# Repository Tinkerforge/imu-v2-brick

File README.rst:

IMU Brick 2.0
=============

This repository contains the firmware source code and the hardware design
files. The documentation generator configs can be found at
https://github.com/Tinkerforge/generators

Repository Content
------------------

software/:
 * examples/: Examples for all supported languages
 * build/: Compiled files
 * src/: Source code of firmware
 * Makefile: Makefile to build project

hardware/:
 * Contains KiCad project files and additionally schematics as PDF

datasheets/:
 * Contains datasheets for sensors and complex ICs that are used

Hardware
--------

The hardware is designed with the open source EDA Suite KiCad
(http://www.kicad.org). Before you are able to open the files,
you have to install the Tinkerforge kicad-libraries
(https://github.com/Tinkerforge/kicad-libraries). You can either clone
them directly in hardware/ or clone them in a separate folder and
symlink them into hardware/
(ln -s kicad_path/kicad-libraries project_path/hardware). After that you
can open the .pro file in hardware/ with KiCad and from there view and
modify the schematics and the PCB layout.

Software
--------

If you want to do your own Brick/Bricklet firmware development we highly
recommend that you use our build environment setup script and read the
tutorial (https://www.tinkerforge.com/en/doc/Tutorials/Tutorial_Build_Environment/Tutorial.html).

To compile the C code we recommend you to install the newest GNU Arm Embedded
Toolchain (https://launchpad.net/gcc-arm-embedded/+download).
You also need to install bricklib (https://github.com/Tinkerforge/bricklib).

You can either clone it directly in software/src/ or clone it in a
separate folder and symlink it into software/src/
(ln -s bricklib_path/bricklib project_path/software/src/). Finally make sure to
have CMake installed (http://www.cmake.org/cmake/resources/software.html).

After that you can build the firmware by invoking make in software/.
The firmware (.bin) can then be found in software/build/ and uploaded
with brickv (click button "Flashing" on start screen).

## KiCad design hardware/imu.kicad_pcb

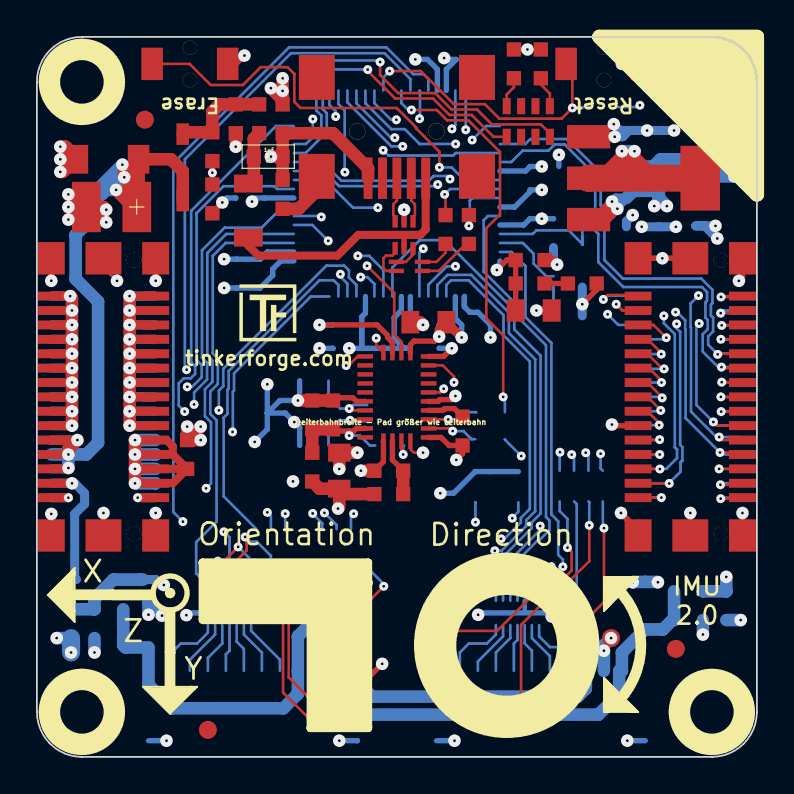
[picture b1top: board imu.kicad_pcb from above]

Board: 4 copper layers, 40.0 x 40.0 mm, 107 parts (0 on the bottom side), 124 nets.

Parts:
C1, C2: DNP; C0603
C3: 1µF; 0603
C4, C401, C402, C403, C404: 1µF; C0603
C5, C6: 22pF; C0603
C7, C8, C14, C17, C18, C19, C20, C22, C23, C24, C26, C27, C29, C30: 100nF; C0603
C9: 6.8nF; C0603
C10: 120nF; C0603
C11: 4.7µF; C0805
C12: 100µF; 3528-21
C13, C16: 10µF; C0805
C15, C28: 4.7µF; C0603
C21: 2.2µF; C0603
C25: 10µF/10V; C0805
D1, D3, D5, D7: blue; D0603
D2, D4, D6, D8: red; D0603
D9, D10, D11, D12: green; D0603
D13, D14: B0520LW-7-F; SOD-123
D15: Z5V; MiniMelf
D16: Z3.3V; MiniMelf
D401: ESD5V0D3B-TP; SOD-323
D402: ESD3V3D3B-TP; SOD-323
F1: PTC; C1206
FB1, FB2, FB4: FB; C0603
FB3: 0; C0603
FB401, FB402: FILTER; C0603
FILTER401, FILTER402: IP4254; DFN16-33x135
Fiducial_Mark: VAL**; Fiducial_Mark
Fiducial_Mark#2, Fiducial_Mark#3, Fiducial_Mark#4, Fiducial_Mark#5, Fiducial_Mark#6: VAL**; Fiducial_Mark
J1: USB-MINI-B-SMD
J2, J3, J4, J5: DRILL; DRILL_NP
J6, J8: STACK-UP-LOW; BTB08-ACS-TOP
J7, J9: STACK-DOWN; BTB08-ACS-BTM
L1: 744230900; WE-CNSW-0603
L2, L3: INDUCTOR; C0603
L4: LBR2012T100K; C0805
P1, P2: CON-SENSOR
R1, R2: 27; R0603
R3: 0; R0603
R4: 47k; R0603
R5: 68k; R0603
R6: 10k; R0603
R7, R8: DNP; R0603
R9: 1k; R0603
R10: 1R0; R0603
RP1, RP2, RP3, RP4, RP5: 1k; 0603X4
SW1: Reset; TACT-SWITCH
SW2: Erase; TACT-SWITCH
U1: AT91SAM3SXB; LQFP64
U2: 82400152; SOT563-SPEC
U3: BNO055; LGA28_5832
U4: LD1117; SOT-223
VAL: CE_5mm
VAL#2: WEEE_7mm
X1: 16Mhz; CRYSTAL_3225
X2: 32.768kHz; AB26TRQ

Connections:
3V3: C11.1, C13.1, C14.1, C15.1, C17.1, C19.1, C20.1, C25.1, C27.1, C30.1, C402.1, D1.1, D2.1, D3.1, D4.1, D5.1, D6.1, D7.1, D8.1, D9.1, D10.1, D11.1, D12.1, D13.1, D16.2, FB402.1, FILTER401.14, J6.20, L2.2, L3.2, RP5.1, RP5.2, RP5.3, RP5.4, SW2.2, U1.1, U1.7, U1.18, U1.45, U1.58, U4.2
BNO-ADR-SELECT: U1.34, U3.17
BNO-BOOT: R6.2, U1.38, U3.4
BNO-INT: U1.26, U3.14
BNO-PIN7: R7.1, U1.52
BNO-PIN8: R8.1, U1.41
BNO-nRESET: U1.35, U3.11
BRICKLET-I2C-SCL: FILTER401.16, FILTER402.16, RP5.5, U1.36, U3.19
BRICKLET-I2C-SDA: FILTER401.15, FILTER402.15, RP5.8, U1.43, U3.20
BRICKLET-IO0_0/AD0: FILTER401.13, U1.4
BRICKLET-IO0_1/DA0: FILTER401.12, U1.63
BRICKLET-IO0_2/PWM0: FILTER401.11, U1.44
BRICKLET-IO0_3: FILTER401.10, U1.19
BRICKLET-IO1_0/AD1: FILTER402.13, U1.3
BRICKLET-IO1_1/DA1: FILTER402.12, U1.59
BRICKLET-IO1_2/PWM1: FILTER402.11, U1.47
BRICKLET-IO1_3: FILTER402.10, U1.9
GND: C1.2, C2.2, C4.2, C5.2, C6.2, C7.2, C8.2, C9.2, C10.2, C11.2, C12.2, C13.2, C14.2, C15.2, C16.2, C17.2, C18.2, C19.2, C20.2, C21.2, C22.2, C23.2, C24.2, C25.2, C26.2, C27.2, C28.2, C29.2, C30.2, C401.2, C402.2, C403.2, C404.2, D15.1, D16.1, D401.1, D402.1, FB3.2, FILTER401.EXP, FILTER402.14, FILTER402.EXP, J6.EP, J7.EP, J8.EP, J9.EP, P1.2, P1.EP, P2.2, P2.EP, R3.1, R5.1, SW1.2, U1.2, U1.17, U1.46, U1.60, U3.2, U3.5, U3.6, U3.10, U3.15, U3.16, U3.18, U3.25, U4.1, X1.3, X2.3
GNDA: C3.2, FB2.1, J1.5, R3.2, U2.2
LED-DEG-1: RP4.1, U1.20
LED-DEG-2: RP4.3, U1.37
LED-DEG-3: RP4.4, U1.48
LED-DEG-4: RP4.2, U1.32
LED-XYZ-XA: RP2.1, U1.15
LED-XYZ-XB: RP2.2, U1.13
LED-XYZ-YA: RP2.3, U1.23
LED-XYZ-YB: RP3.1, U1.16
LED-XYZ-ZA: RP3.2, U1.25
LED-XYZ-ZB: RP3.3, U1.42
unnamed: C3.1, F1.2, FB1.1
unnamed: C5.1, U3.27, X2.2
unnamed: C6.1, U3.26, X2.1
unnamed: C7.1, U3.9
unnamed: C8.1, L3.1, U3.3
unnamed: C9.1, C10.1, L2.1, R6.1, U3.28
unnamed: C21.1, C22.1, C23.1, C24.1, C26.1, L4.1, U1.8, U1.12, U1.24, U1.54
unnamed: C28.1, R10.1
unnamed: C29.1, L4.2, R10.2, U1.64
unnamed: C403.1, D401.2, FB401.2, P1.1, P2.1
unnamed: C404.1, D402.2, FB402.2, P1.3, P2.3
unnamed: D1.2, RP1.1
unnamed: D2.2, RP1.4
unnamed: D3.2, RP2.8
unnamed: D4.2, RP2.7
unnamed: D5.2, RP2.6
unnamed: D6.2, RP3.8
unnamed: D7.2, RP3.7
unnamed: D8.2, RP3.6
unnamed: D9.2, RP4.8
unnamed: D10.2, RP4.7
unnamed: D11.2, RP4.6
unnamed: D12.2, RP4.5
unnamed: D13.2, J8.28, J9.28
unnamed: F1.1, J1.1, U2.5
unnamed: FB2.2, J1.6
unnamed: FB3.1, J8.21, J8.23, J8.25, J8.27, J9.21, J9.23, J9.25, J9.27
unnamed: FB4.2, J8.22, J8.24, J8.26, J9.22, J9.24, J9.26
unnamed: FILTER401.1, P1.4
unnamed: FILTER401.2, P1.5
unnamed: FILTER401.3, P1.6
unnamed: FILTER401.4, P1.7
unnamed: FILTER401.5, P1.8
unnamed: FILTER401.6, P1.9
unnamed: FILTER401.7, P1.10
unnamed: FILTER402.1, P2.4
unnamed: FILTER402.2, P2.5
unnamed: FILTER402.3, P2.6
unnamed: FILTER402.4, P2.7
unnamed: FILTER402.5, P2.8
unnamed: FILTER402.6, P2.9
unnamed: FILTER402.7, P2.10
unnamed: J1.2, U2.1
unnamed: J1.3, U2.3
unnamed: J6.6, J7.8
unnamed: J6.7, J7.7, R9.1
unnamed: J6.8, J7.10
unnamed: J6.10, J7.12
unnamed: J6.12, J7.14
unnamed: J6.13, J7.13
unnamed: J6.14, J7.16
unnamed: J6.15, J7.15
unnamed: J6.16, J7.18
unnamed: J6.17, J7.17
unnamed: J6.18, J7.20
unnamed: J6.22, J7.22
unnamed: J6.24, J7.24
unnamed: J6.25, J7.25
unnamed: J6.27, J7.27
unnamed: J6.29, J7.29
unnamed: J6.30, J7.30
unnamed: J8.1, J8.3, J8.5, J8.7, J8.9, J8.11, J8.13, J8.15, J8.17, J8.19, J9.1, J9.3, J9.5, J9.7, J9.9, J9.11, J9.13, J9.15, J9.17, J9.19
unnamed: J8.2, J8.4, J8.6, J8.8, J8.10, J8.12, J8.14, J8.16, J8.18, J8.20, J9.2, J9.4, J9.6, J9.8, J9.10, J9.12, J9.14, J9.16, J9.18, J9.20
unnamed: J8.29, J9.29
unnamed: J8.30, J9.30
unnamed: L1.1, R2.1
unnamed: L1.2, U2.4
unnamed: L1.3, U2.6
unnamed: L1.4, R1.1
unnamed: R1.2, U1.56
unnamed: R2.2, U1.57
unnamed: R7.2, U3.7
unnamed: R8.2, U3.8
unnamed: RP1.5, U1.29
unnamed: RP1.8, U1.30
unnamed: SW2.1, U1.55
STACK-DETECT/JTAG-TMS: J6.9, J7.9, U1.51
STACK-I2C-SCL/JTAG-TDO: J6.4, J7.4, U1.49
STACK-I2C-SDA/JTAG-TDI: J6.2, J7.2, U1.33
STACK-INT0: J6.19, J7.19, U1.6
STACK-INT1: J6.21, J7.21, U1.31
STACK-INT2: J6.23, J7.23, U1.10
STACK-RESET: R9.2, SW1.1, U1.39
STACK-SER-RXD: J6.26, J7.26, U1.11
STACK-SER-TXD: J6.28, J7.28, U1.14
STACK-SPI-MISO: J6.1, J7.1, U1.27
STACK-SPI-MOSI: J6.3, J7.3, U1.22
STACK-SPI-SCLK: J6.5, J7.5, U1.21
STACK-SPI-SELECT: J7.6, U1.28
STACK-SYNC/JTAG-TCK: J6.11, J7.11, U1.53
USB-DETECT: R4.1, R5.2, U1.5
VSTACK: C12.1, C16.1, C18.1, C401.1, D14.2, D15.2, FB4.1, FB401.1, U4.3
VUSB: C4.1, D14.1, FB1.2, R4.2
XIN: C2.1, U1.62, X1.2
XOUT: C1.1, U1.61, X1.1

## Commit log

2015-03-26 add hardware files for imu v2
2015-03-26 add schematic
2015-03-31 increase signal to border distance
2015-04-01 route signals with more distance to border
2015-04-07 Add BNO055 datasheet
2015-04-08 Add first stub implementation of IMU Brick 2.0
    Currently mostly copied from IMU Brick 1.0
2015-04-08 Add "2.0" to product descriptor
2015-04-08 Add sensor data unit information
2015-04-08 Remove unused function declarations
2015-04-09 Implement API for new IMU 2.0 features
2015-04-10 Implement missing API
2015-04-10 Remove unneeded libm
2015-04-14 Remove configuration, add calibration
2015-04-14 Put IMU in in config mode before ext clk enable
2015-04-16 Fix display name in readme
2015-04-16 Add .gitignore
2015-04-23 change footprint of bno055 crystal
2015-04-30 Add Python example
2015-04-30 Use nicer formatting
2015-05-07 fix tvs diode orientation, fix component texts
2015-05-07 change some routing, change drill positions, change silkscreen
2015-05-07 Add C# example
2015-05-07 Add VB.NET example
2015-05-07 Add Delphi example
2015-05-07 Add Java examples
2015-05-07 Add C examples
2015-05-07 Add JavaScript examples
2015-05-07 Add Perl example
2015-05-07 Add PHP example
2015-05-07 Add Ruby example
2015-05-07 Add Shell example
2015-06-15 Adding MATLAB/Octave exmaples
2015-06-18 Whitespace cleanup in examples
2015-06-22 Fix wrong order, add comment
2015-06-24 Add LabVIEW and update Mathematica examples
    Also clean up other examples and add all-data examples.
2015-06-24 ruby: Fix syntax error and set all-data period
2015-06-25 octave: Handle short/byte difference between Octave 3.6 and 3.8
    In Octave 3.6 a short/byte is not automatically handled as a number.
2015-06-29 Fix typo in MATLAB example
2015-07-08 MATLAB example fixes
2015-07-10 matlab: Fix quaternion order
2015-07-23 Make JavaScript browser example textarea readonly
2015-07-27 Cleanup C/C++, C#, Java, Python and Ruby examples
2015-07-29 Reformat changelog
2015-08-07 Use full device class name in Python examples
2015-08-12 Fix minor warnings in C/C++ examples
2015-08-14 Cleanup Delphi examples
2015-08-18 Cleanup VB.NET examples
2015-08-19 Cleanup Perl examples
2015-08-19 Read the IMU data in 10 different stages
2015-08-19 Remove double increment of sensor counter
2015-08-24 Remove WIP marker from readme
2015-09-10 Duplicate cmake call to fix bug during cmake creation
    Also, toolchain is now in bricklib.
2015-09-17 javascript: Print calibration status as bitmask
2015-10-21 Generator based example cleanup
2015-10-26 Fix wrong order of callbacks
2015-10-26 Fix wrong FID order too
2015-11-12 matlab: Fix callback handling for R2014a
    http://undocumentedmatlab.com/blog/matlab-callbacks-for-java-events-in-r2014a
2015-11-25 Include date and commit into changelog
2016-01-13 Saving of calibration currently only on sam3s
    We added support for the sam4s processor family to bricklib, saving the
    calibration to the flash is currently not possible with the old code. We just
    remove it for sam4s for now (we will fix it if there actually is a IMU Brick
    with the sam4s)
2016-02-09 Fix possible data corruption if getters are called with high frequency
2016-02-09 Add changelog commit after the fact
2016-02-25 Use DMA for I2C communication with BNO055
    This allows for better SPI stack communication throughput, since
    we don't have to disable the interrupts for the whole communication
2016-05-18 c: Add missing device destroy call
2016-07-01 Make the change UID comment more explicit
2016-07-25 fix diode symbols
2016-08-29 Make sure to use all chunks when writing firmware
    Change through Bricklib
2016-08-29 Fix changelog date
2016-08-30 Better changelog wording
2016-12-05 dd ringbuffer and system timer utility as well as co_mcu support files to Makefile (all added through bricklib)
2017-01-06 Add COM_MESSAGE_USER_LAST_FID define (needed for newest bricklib)
2017-01-27 Add support for fusion mode and sensor configuration
2017-01-27 Remove unused code
2017-01-31 Remove wrong comment about callback period from examples
2017-02-03 Add support for fusion mode without magnetometer
2017-02-03 Add 2.0.6 changelog ref
2017-03-16 Move I2C mutex handling outside of interrupt.
    This fixes a race condition with the Accelerometer Bricklet (and potentially other Bricklets that use I2C),
2017-03-16 Add ref for 2.0.7
2017-04-13 csharp: Adapt example
2017-04-13 matlab: Fix typo
2017-05-11 Add support for co-mcu Bricklets
2017-05-11 Add ref for last changelog entry
2017-06-02 Update footprints for 3d
2017-06-02 Add some 3d components
2017-06-02 Fix footprints
2017-06-02 Add all 3d information
2017-06-02 Add 3D model for IMUv2 Brick
2017-06-02 octave: Use javaObject instead of deprecated java_new
2017-06-28 Update changelog and version
2017-06-28 Add tag ref to changelog
2017-06-30 3d: New version of tactile switches
2017-11-30 Update examples from generator
2017-12-05 Remove initial USB enumeration (now done in bricklib)
2017-12-05 Increase firmware version, update changelog
2017-12-07 mathematica: Also generate .nb files
2017-12-12 Remove unused include
2017-12-12 Remove unused variable
2017-12-12 Match external variable name (renamed in Brick Viewer)
2017-12-13 Increase TWI priority
2017-12-13 Add date and ref to changelog
2018-01-11 Increase version number (message duplication bug fix through bricklib)
2018-01-11 Add ref to changelog
2018-01-30 Update examples
2018-02-19 javascript: Close div tag correctly
2018-02-20 Cleanup KiCad libraries config
    Ensure LibDir=kicad-libraries and LibName1=tinkerforge.
    Remove special library.
2018-04-27 Remove unnecessary return
    This actually broke the callback period timing...
2018-04-27 Add calibration support for SAM4 microcontroller
2018-04-27 Remove debugging
2018-04-27 Update changelog
2018-04-27 Fix date
2018-04-27 Add git ref to changelog
2018-05-24 perl: Use strict in examples
2018-05-28 mathematica: Reorder some lines for clearity
2018-07-11 Add Makefile with docker support
2018-07-11 Remove obsolete generate_makefile scripts
2018-07-11 Update directory structure and build instructions
2018-07-20 Add support for fusion mode without fast magnetometer calibration
2018-07-20 Add ref for 2.0.13
2018-07-25 Add new 3d model
2018-07-31 Add missing 2.0.13 changes to changelog
2018-09-03 Unify spelling in changelog
2018-11-07 rust: Accept host names for ip connection, fix naming inconsistencies
2018-11-07 rust: Rename callback receivers.
2018-12-14 Add go examples.
2018-12-14 go: Fix printf parameters.
2018-12-18 go: Change import path.
2018-12-18 go: Change import path again.
2018-12-20 rust: Fix result variable names in examples.
2018-12-20 rust: Reformat examples.
2019-01-24 mqtt: Add examples.
2019-01-24 mqtt: Fix example header.
2019-01-24 mqtt: Remove executable bit in example permissions.
2019-01-24 go: Minor example fixes.
2019-01-24 mqtt: Minor example fixes.
2019-02-27 Increase version for new release (changes in bricklib)
2019-02-27 Add rev to changelog
2019-03-28 mqtt: Fix whitespace.
2019-05-15 add the imu 3d model with silkscreen
2019-05-15 add the .step
2019-08-22 c: Adapt to bindings changes
2019-12-02 examples: Use Euler angle names
2020-01-13 Add simple csv logger example
2020-01-13 examples: Use python3 input instead of python2 raw_input.
2020-01-13 examples: mqtt: Remove trailing whitespace.
2020-02-20 v3 prototype initial push
2021-03-23 Fix temperature callback response size.
2021-03-23 Increase version for new release.
2021-03-23 Add commit ref to changelog.
2021-10-25 Update KiCad link
    https://www.kicad.org/blog/2021/10/Avoid-links-to-former-kicad-domain/
2022-07-06 Add license files.

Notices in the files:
hardware/imu.kicad_pcb:
Licensed under CERN OHL v.1.1
Copyright (©) 2015, B.Nordmeyer
Copyright Tinkerforge GmbH 2015.
This documentation describes Open Hardware and is licensed under the
CERN OHL v. 1.1.
